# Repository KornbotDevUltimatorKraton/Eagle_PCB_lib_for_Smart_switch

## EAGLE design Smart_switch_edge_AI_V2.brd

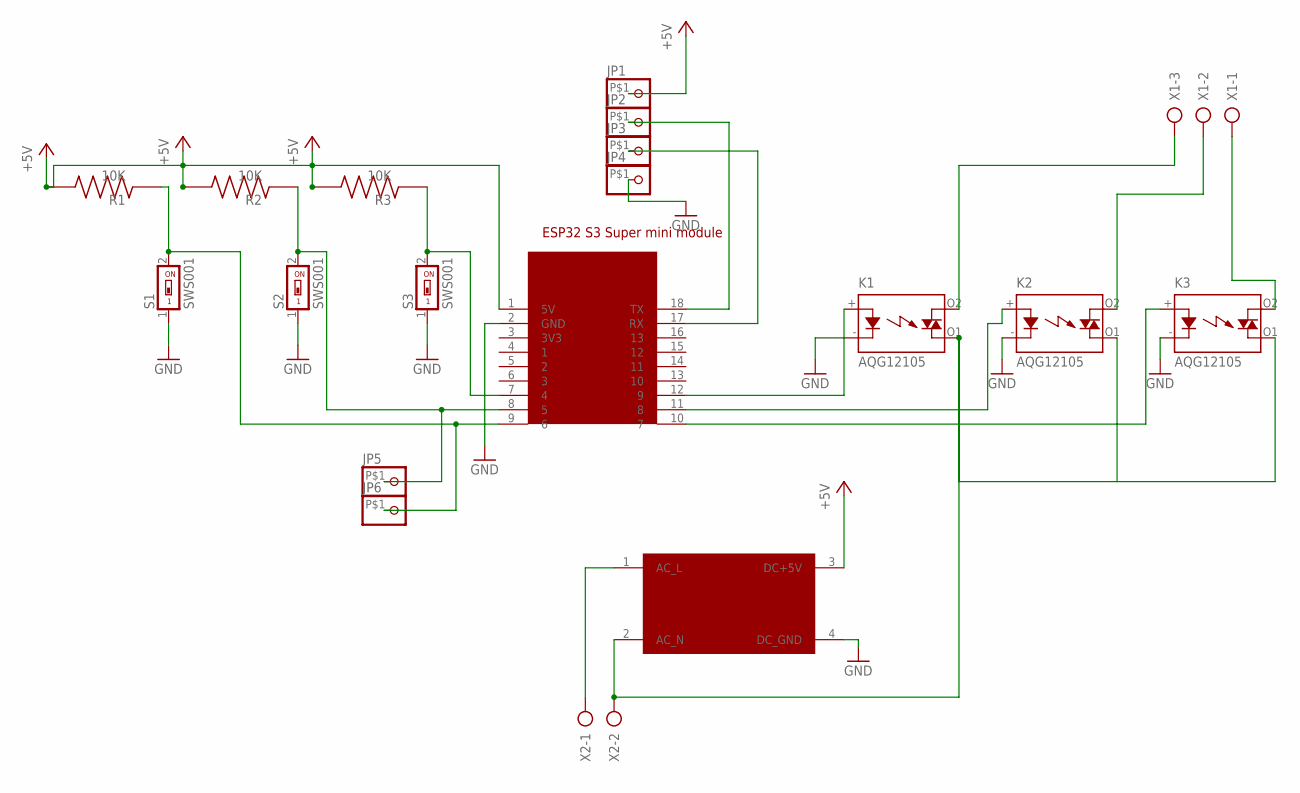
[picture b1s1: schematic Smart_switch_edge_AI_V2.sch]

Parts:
JP1, JP2, JP3, JP4, JP5, JP6: PINHD-1X1-BIGPOGO; 1X1-BIGPOGO
K1, K2, K3: AQG12105; AQG
R1, R2, R3: 10K; RES_ERA6ARB512V
S1, S2, S3: SWS001; SMS-001
U$1: ESP32_S3_SUPERMINI; SON270P1795X2385X160-18N
U$2: AL0505F; DIP1650W60P600L1447H300Q4B
X1: AK500/3
X2: AK500/2

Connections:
+5V: JP1.P$1, R1.2, R2.2, R3.2, U$1.1 (5V), U$2.3 (DC+5V)
GND: JP4.P$1, K1.- (K), K2.- (K), K3.- (K), S1.1, S2.1, S3.1, U$1.2 (GND), U$2.4 (DC_GND)
unnamed: JP6.P$1, R1.1, S1.2, U$1.9 (6)
unnamed: JP5.P$1, R2.1, S2.2, U$1.8 (5)
unnamed: R3.1, S3.2, U$1.7 (4)
unnamed: K1.+ (A), U$1.12 (9)
unnamed: K2.+ (A), U$1.11 (8)
unnamed: K3.+ (A), U$1.10 (7)
unnamed: K1.O2 (DS1), X1.3
unnamed: K2.O2 (DS1), X1.2
unnamed: K3.O2 (DS1), X1.1
unnamed: K1.O1 (DS2), K2.O1 (DS2), K3.O1 (DS2), U$2.2 (AC_N), X2.2
unnamed: U$2.1 (AC_L), X2.1
unnamed: JP2.P$1, U$1.18 (TX)
unnamed: JP3.P$1, U$1.17 (RX)

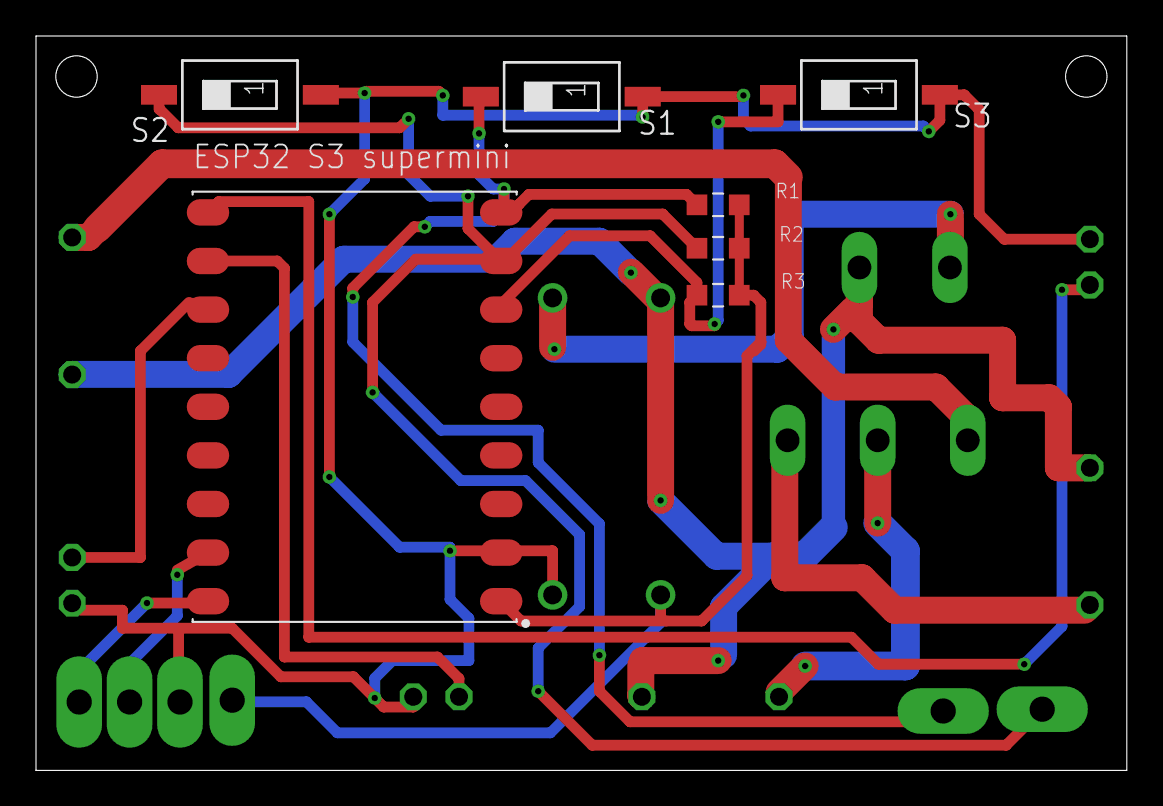
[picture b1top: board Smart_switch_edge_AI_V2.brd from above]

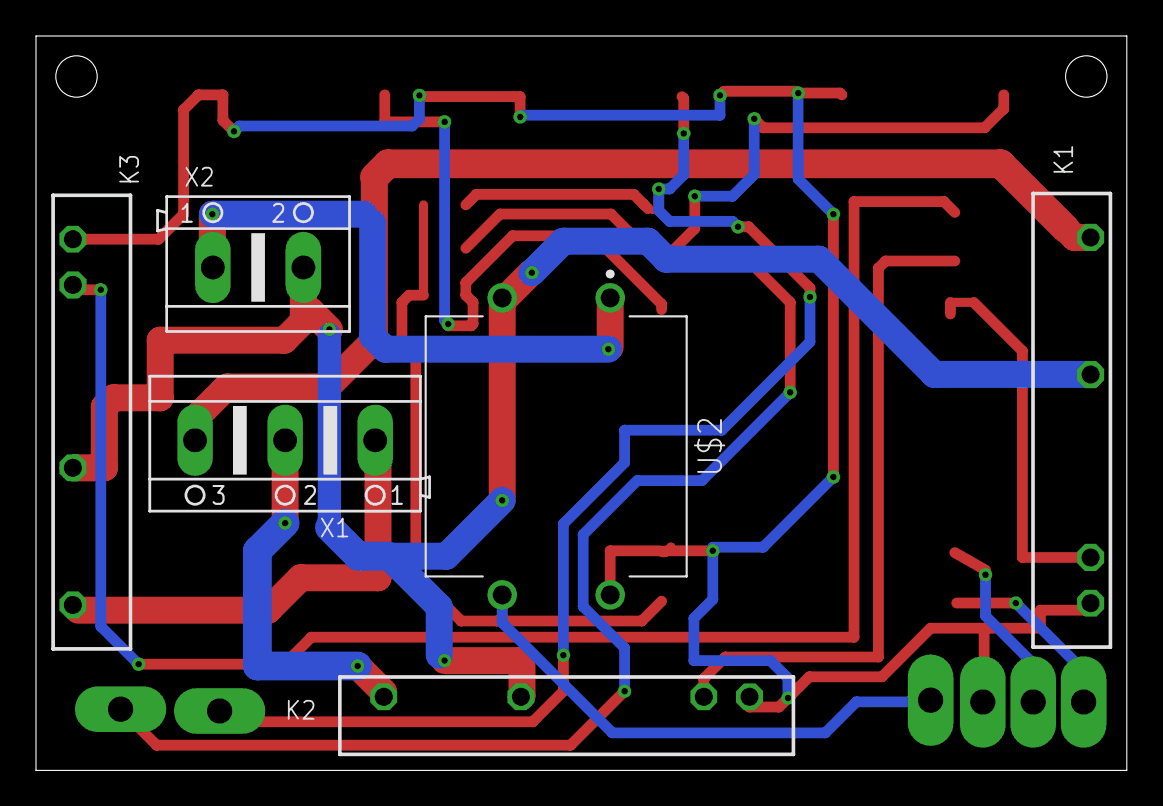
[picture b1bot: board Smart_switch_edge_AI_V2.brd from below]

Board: 2 copper layers, 60.6 x 40.8 mm, 19 parts (10 on the bottom side), 15 nets.
